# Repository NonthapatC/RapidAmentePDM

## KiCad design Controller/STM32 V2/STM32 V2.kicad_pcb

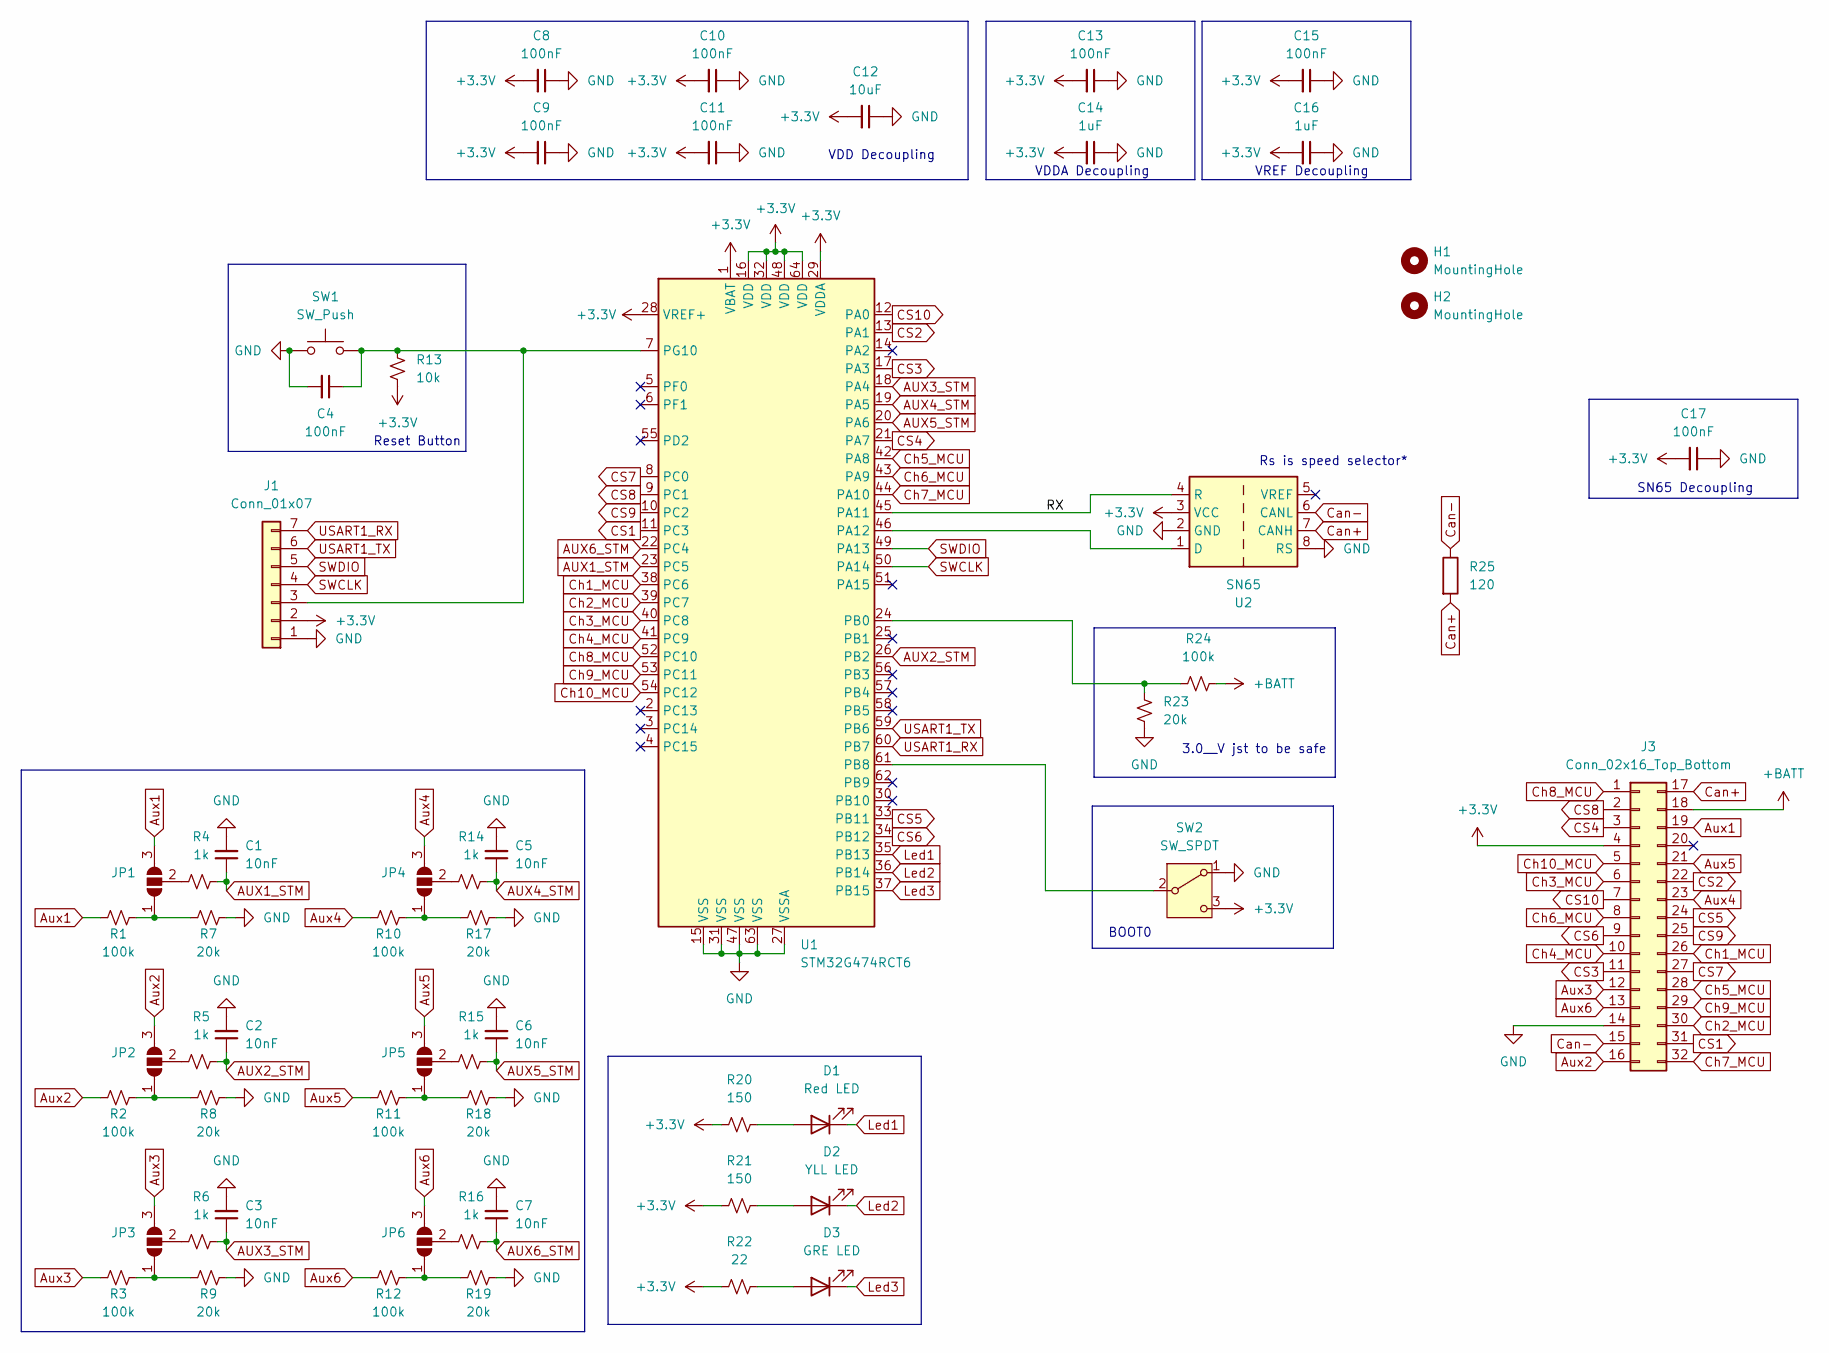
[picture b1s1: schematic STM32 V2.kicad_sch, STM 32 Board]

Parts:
C1, C2, C3, C5, C6, C7: 10nF; C_0805_2012Metric_Pad1.18x1.45mm_HandSolder
C4, C8, C9, C10, C11, C13, C15, C17: 100nF; C_0805_2012Metric_Pad1.18x1.45mm_HandSolder
C12: 10uF; C_0805_2012Metric_Pad1.18x1.45mm_HandSolder
C14, C16: 1uF; C_0805_2012Metric_Pad1.18x1.45mm_HandSolder
D1: Red LED; LED_0805_2012Metric_Pad1.15x1.40mm_HandSolder
D2: YLL LED; LED_0805_2012Metric_Pad1.15x1.40mm_HandSolder
D3: GRE LED; LED_0805_2012Metric_Pad1.15x1.40mm_HandSolder
H1, H2: MountingHole; MountingHole_NPTH_3.5_6.25SB
J1: Conn_01x07; PinSocket_1x07_P2.54mm_Vertical
J3: Conn_02x16_Top_Bottom; PinSocket_2x16_P2.54mm_Vertical
JP1, JP2, JP3, JP4, JP5, JP6: SolderJumper_3_Open; SolderJumper-3_P1.3mm_Open_RoundedPad1.0x1.5mm_NumberLabels
R1, R2, R3, R10, R11, R12, R24: 100k; R_0805_2012Metric_Pad1.20x1.40mm_HandSolder
R4, R5, R6, R14, R15, R16: 1k; R_0805_2012Metric_Pad1.20x1.40mm_HandSolder
R7, R8, R9, R17, R18, R19, R23: 20k; R_0805_2012Metric_Pad1.20x1.40mm_HandSolder
R13: 10k; R_0805_2012Metric_Pad1.20x1.40mm_HandSolder
R20, R21: 150; R_0805_2012Metric_Pad1.20x1.40mm_HandSolder
R22: 22; R_0805_2012Metric_Pad1.20x1.40mm_HandSolder
R25: 120; R_0805_2012Metric_Pad1.20x1.40mm_HandSolder
SW1: SW_Push; SW_SPST_PTS647_Sx38
SW2: SW_SPDT; HOOYA MK-12D13G4-B
U1: STM32G474RCT6; LQFP-64_10x10mm_P0.5mm
U2: SN65; SOIC-8_3.9x4.9mm_P1.27mm

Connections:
+3.3V: C8.2, C9.2, C10.2, C11.2, C12.2, C13.2, C14.2, C15.2, C16.2, C17.2, J1.2, J3.4, R13.2, R20.2, R21.2, R22.2, SW2.3 (C), U1.1 (VBAT), U1.16 (VDD), U1.28 (VREF+), U1.29 (VDDA), U1.32 (VDD), U1.48 (VDD), U1.64 (VDD), U2.3 (VCC)
+BATT: J3.18, R24.2
/RX: U1.45 (PA11), U2.4 (R)
AUX1_STM: C1.1, R4.2, U1.23 (PC5)
AUX2_STM: C2.1, R5.2, U1.26 (PB2)
AUX3_STM: C3.1, R6.2, U1.18 (PA4)
AUX4_STM: C5.1, R14.2, U1.19 (PA5)
AUX5_STM: C6.1, R15.2, U1.20 (PA6)
AUX6_STM: C7.1, R16.2, U1.22 (PC4)
Aux1: J3.19, JP1.3 (B), R1.1
Aux2: J3.16, JP2.3 (B), R2.1
Aux3: J3.12, JP3.3 (B), R3.1
Aux4: J3.23, JP4.3 (B), R10.1
Aux5: J3.21, JP5.3 (B), R11.1
Aux6: J3.13, JP6.3 (B), R12.1
CS1: J3.31, U1.11 (PC3)
CS2: J3.22, U1.13 (PA1)
CS3: J3.11, U1.17 (PA3)
CS4: J3.3, U1.21 (PA7)
CS5: J3.24, U1.33 (PB11)
CS6: J3.9, U1.34 (PB12)
CS7: J3.27, U1.8 (PC0)
CS8: J3.2, U1.9 (PC1)
CS9: J3.25, U1.10 (PC2)
CS10: J3.7, U1.12 (PA0)
Can+: J3.17, R25.2, U2.7 (CANH)
Can-: J3.15, R25.1, U2.6 (CANL)
Ch1_MCU: J3.26, U1.38 (PC6)
Ch2_MCU: J3.30, U1.39 (PC7)
Ch3_MCU: J3.6, U1.40 (PC8)
Ch4_MCU: J3.10, U1.41 (PC9)
Ch5_MCU: J3.28, U1.42 (PA8)
Ch6_MCU: J3.8, U1.43 (PA9)
Ch7_MCU: J3.32, U1.44 (PA10)
Ch8_MCU: J3.1, U1.52 (PC10)
Ch9_MCU: J3.29, U1.53 (PC11)
Ch10_MCU: J3.5, U1.54 (PC12)
GND: C1.2, C2.2, C3.2, C4.2, C5.2, C6.2, C7.2, C8.1, C9.1, C10.1, C11.1, C12.1, C13.1, C14.1, C15.1, C16.1, C17.1, J1.1, J3.14, R7.2, R8.2, R9.2, R17.2, R18.2, R19.2, R23.1, SW1.1, SW2.1 (A), U1.15 (VSS), U1.27 (VSSA), U1.31 (VSS), U1.47 (VSS), U1.63 (VSS), U2.2 (GND), U2.8 (RS)
Led1: D1.1 (K), U1.35 (PB13)
Led2: D2.1 (K), U1.36 (PB14)
Led3: D3.1 (K), U1.37 (PB15)
unnamed: D1.2 (A), R20.1
unnamed: D2.2 (A), R21.1
unnamed: D3.2 (A), R22.1
unnamed: C4.1, J1.3, R13.1, SW1.2, U1.7 (PG10)
unnamed: JP1.1 (A), R1.2, R7.1
unnamed: JP1.2 (C), R4.1
unnamed: JP2.1 (A), R2.2, R8.1
unnamed: JP2.2 (C), R5.1
unnamed: JP3.1 (A), R3.2, R9.1
unnamed: JP3.2 (C), R6.1
unnamed: JP4.1 (A), R10.2, R17.1
unnamed: JP4.2 (C), R14.1
unnamed: JP5.1 (A), R11.2, R18.1
unnamed: JP5.2 (C), R15.1
unnamed: JP6.1 (A), R12.2, R19.1
unnamed: JP6.2 (C), R16.1
unnamed: SW2.2 (B), U1.61 (PB8)
unnamed: U1.46 (PA12), U2.1 (D)
unnamed: R23.2, R24.1, U1.24 (PB0)
SWCLK: J1.4, U1.50 (PA14)
SWDIO: J1.5, U1.49 (PA13)
USART1_RX: J1.7, U1.60 (PB7)
USART1_TX: J1.6, U1.59 (PB6)

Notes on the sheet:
BOOT0
SN65 Decoupling
VDD Decoupling
Reset Button
VREF Decoupling
VDDA Decoupling
3.0__V jst to be safe
Rs is speed selector*

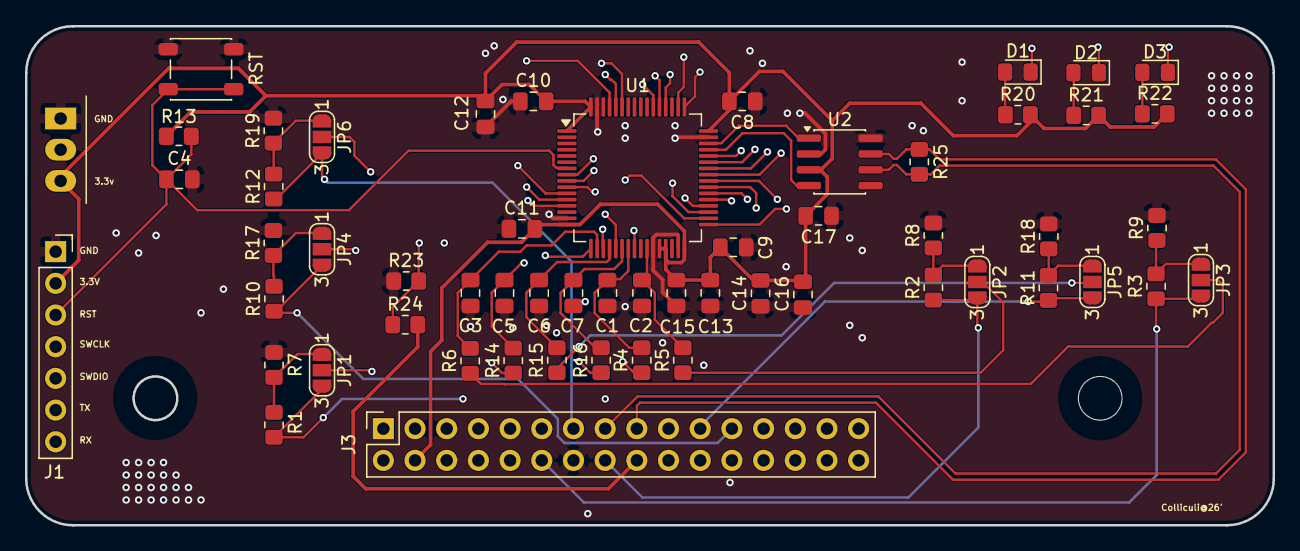
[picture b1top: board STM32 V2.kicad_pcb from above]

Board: 4 copper layers, 100.0 x 40.0 mm, 59 parts (0 on the bottom side), 64 nets.

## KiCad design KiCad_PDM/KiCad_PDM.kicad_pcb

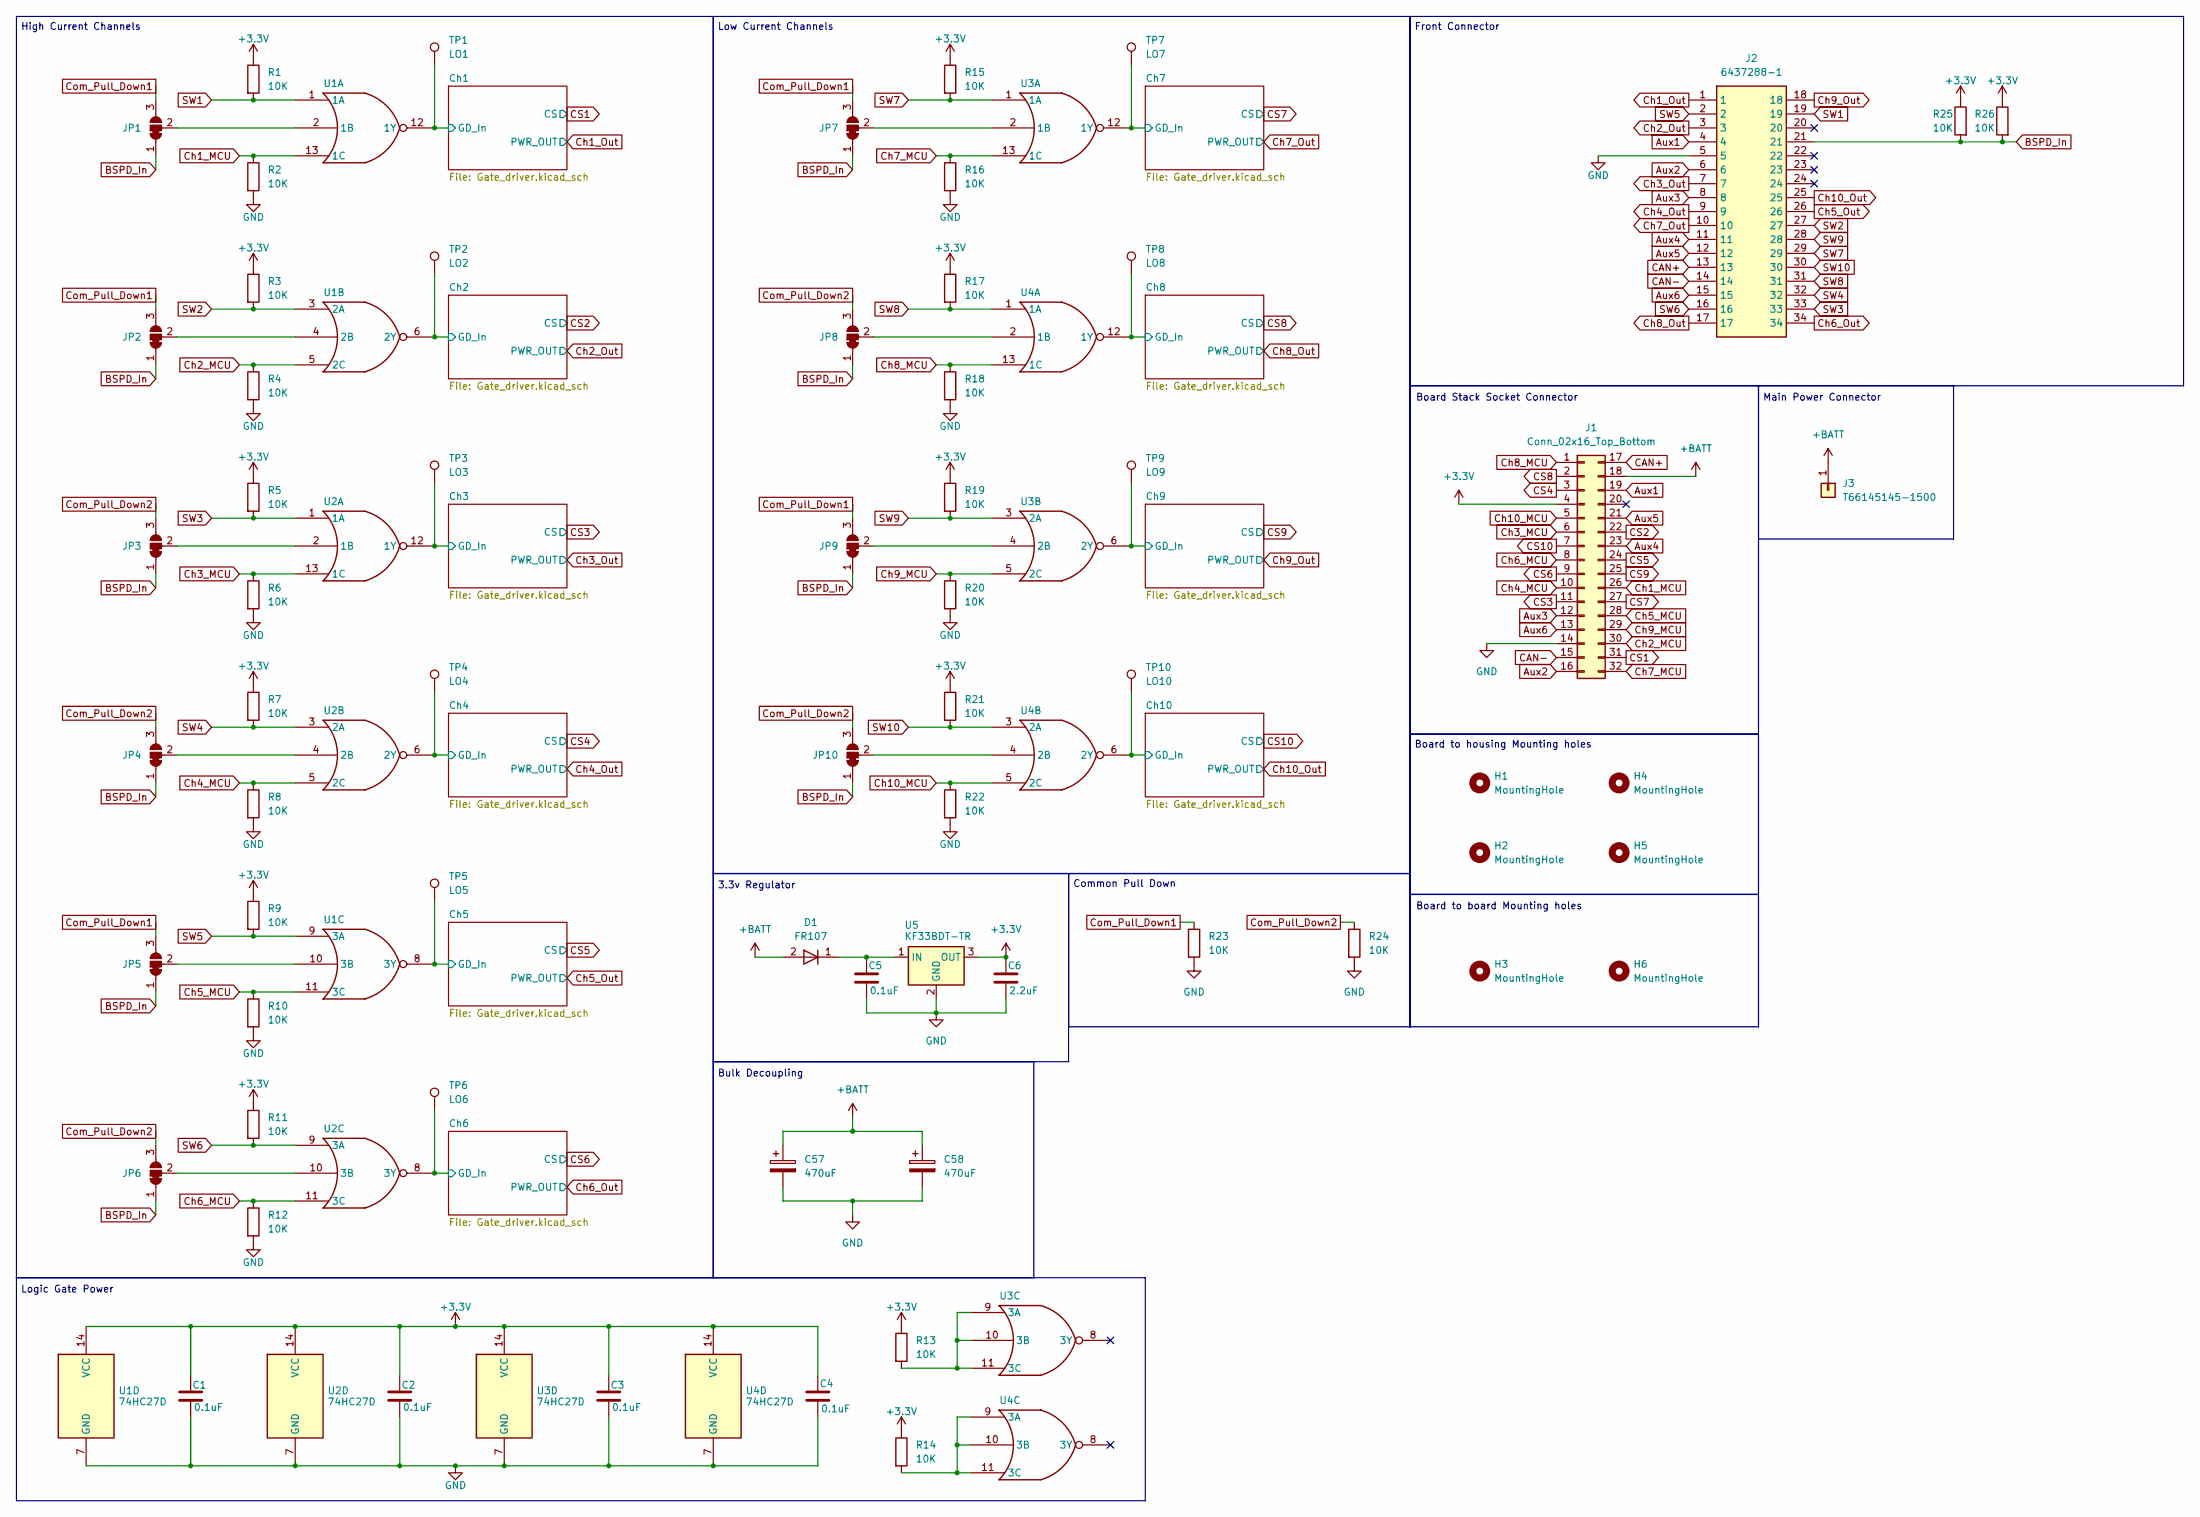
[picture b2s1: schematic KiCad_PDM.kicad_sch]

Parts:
C1, C2, C3, C4, C5: 0.1uF; C_0805_2012Metric_Pad1.18x1.45mm_HandSolder
C6: 2.2uF; C_0805_2012Metric_Pad1.18x1.45mm_HandSolder
C57, C58: 470uF; CP_Radial_D8.0mm_P2.50mm
D1: FR107; D_SOD-123
H1, H2, H3, H4, H5, H6: MountingHole; MountingHole_NPTH_3.5_6.25SB
J1: Conn_02x16_Top_Bottom; PinSocket_2x16_P2.54mm_Vertical
J2: 6437288-1; Mouser Part Number 571-6437288-1
J3: T66145145-1500; XFCN T66145145-1500
JP1, JP2, JP3, JP4, JP5, JP6, JP7, JP8, JP9, JP10: SolderJumper_3_Bridged12; SolderJumper-3_P1.3mm_Bridged2Bar12_RoundedPad1.0x1.5mm_Num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
R1, R2, R3, R4, R5, R6, R7, R8, R9, R10, R11, R12, R13, R14, R15, R16, R17, R18, R19, R20, R21, R22, R23, R24, R25, R26: 10K; R_0805_2012Metric_Pad1.20x1.40mm_HandSolder
TP1: LO1; Custom_Testpad
TP2: LO2; Custom_Testpad
TP3: LO3; Custom_Testpad
TP4: LO4; Custom_Testpad
TP5: LO5; Custom_Testpad
TP6: LO6; Custom_Testpad
TP7: LO7; Custom_Testpad
TP8: LO8; Custom_Testpad
TP9: LO9; Custom_Testpad
TP10: LO10; Custom_Testpad
U1, U2, U3, U4: 74HC27D; SOIC-14_3.9x8.7mm_P1.27mm
U5: KF33BDT-TR; TO-252-2

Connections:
+3.3V: C1.1, C2.1, C3.1, C4.1, C6.1, J1.4, R1.1, R3.1, R5.1, R7.1, R9.1, R11.1, R13.1, R14.1, R15.1, R17.1, R19.1, R21.1, R25.1, R26.1, U1.14 (VCC), U2.14 (VCC), U3.14 (VCC), U4.14 (VCC), U5.3 (OUT); also elsewhere on the board
+BATT: C57.1, C58.1, D1.2, J1.18, J3.1 (Pin_1_1); also elsewhere on the board
/Ch1/GD_In: TP1.1 (1_1), U1.12 (1Y); also elsewhere on the board
/Ch2/GD_In: TP2.1 (1_1), U1.6 (2Y); also elsewhere on the board
/Ch3/GD_In: TP3.1 (1_1), U2.12 (1Y); also elsewhere on the board
/Ch4/GD_In: TP4.1 (1_1), U2.6 (2Y); also elsewhere on the board
/Ch5/GD_In: TP5.1 (1_1), U1.8 (3Y); also elsewhere on the board
/Ch6/GD_In: TP6.1 (1_1), U2.8 (3Y); also elsewhere on the board
/Ch7/GD_In: TP7.1 (1_1), U3.12 (1Y); also elsewhere on the board
/Ch8/GD_In: TP8.1 (1_1), U4.12 (1Y); also elsewhere on the board
/Ch9/GD_In: TP9.1 (1_1), U3.6 (2Y); also elsewhere on the board
/Ch10/GD_In: TP10.1 (1_1), U4.6 (2Y); also elsewhere on the board
Aux1: J1.19, J2.4
Aux2: J1.16, J2.6
Aux3: J1.12, J2.8
Aux4: J1.23, J2.11
Aux5: J1.21, J2.12
Aux6: J1.13, J2.15
BSPD_In: J2.21, JP1.1 (A), JP2.1 (A), JP3.1 (A), JP4.1 (A), JP5.1 (A), JP6.1 (A), JP7.1 (A), JP8.1 (A), JP9.1 (A), JP10.1 (A), R25.2, R26.2
CAN+: J1.17, J2.13
CAN-: J1.15, J2.14
CS1: J1.31; also elsewhere on the board
CS2: J1.22; also elsewhere on the board
CS3: J1.11; also elsewhere on the board
CS4: J1.3; also elsewhere on the board
CS5: J1.24; also elsewhere on the board
CS6: J1.9; also elsewhere on the board
CS7: J1.27; also elsewhere on the board
CS8: J1.2; also elsewhere on the board
CS9: J1.25; also elsewhere on the board
CS10: J1.7; also elsewhere on the board
Ch1_MCU: J1.26, R2.1, U1.13 (1C)
Ch1_Out: J2.1; also elsewhere on the board
Ch2_MCU: J1.30, R4.1, U1.5 (2C)
Ch2_Out: J2.3; also elsewhere on the board
Ch3_MCU: J1.6, R6.1, U2.13 (1C)
Ch3_Out: J2.7; also elsewhere on the board
Ch4_MCU: J1.10, R8.1, U2.5 (2C)
Ch4_Out: J2.9; also elsewhere on the board
Ch5_MCU: J1.28, R10.1, U1.11 (3C)
Ch5_Out: J2.26; also elsewhere on the board
Ch6_MCU: J1.8, R12.1, U2.11 (3C)
Ch6_Out: J2.34; also elsewhere on the board
Ch7_MCU: J1.32, R16.1, U3.13 (1C)
Ch7_Out: J2.10; also elsewhere on the board
Ch8_MCU: J1.1, R18.1, U4.13 (1C)
Ch8_Out: J2.17; also elsewhere on the board
Ch9_MCU: J1.29, R20.1, U3.5 (2C)
Ch9_Out: J2.18; also elsewhere on the board
Ch10_MCU: J1.5, R22.1, U4.5 (2C)
Ch10_Out: J2.25; also elsewhere on the board
Com_Pull_Down1: JP1.3 (B), JP2.3 (B), JP5.3 (B), JP7.3 (B), JP9.3 (B), R23.1
Com_Pull_Down2: JP3.3 (B), JP4.3 (B), JP6.3 (B), JP8.3 (B), JP10.3 (B), R24.1
GND: C1.2, C2.2, C3.2, C4.2, C5.2, C6.2, C57.2, C58.2, J1.14, J2.5, R2.2, R4.2, R6.2, R8.2, R10.2, R12.2, R16.2, R18.2, R20.2, R22.2, R23.2, R24.2, U1.7 (GND), U2.7 (GND), U3.7 (GND), U4.7 (GND), U5.2 (GND); also elsewhere on the board
unnamed: JP1.2 (C), U1.2 (1B)
unnamed: JP2.2 (C), U1.4 (2B)
unnamed: JP3.2 (C), U2.2 (1B)
unnamed: JP4.2 (C), U2.4 (2B)
unnamed: JP5.2 (C), U1.10 (3B)
unnamed: JP6.2 (C), U2.10 (3B)
unnamed: JP7.2 (C), U3.2 (1B)
unnamed: JP8.2 (C), U4.2 (1B)
unnamed: JP9.2 (C), U3.4 (2B)
unnamed: JP10.2 (C), U4.4 (2B)
unnamed: R13.2, U3.9 (3A), U3.10 (3B), U3.11 (3C)
unnamed: R14.2, U4.9 (3A), U4.10 (3B), U4.11 (3C)
unnamed: C5.1, D1.1, U5.1 (IN)
SW1: J2.19, R1.2, U1.1 (1A)
SW2: J2.27, R3.2, U1.3 (2A)
SW3: J2.33, R5.2, U2.1 (1A)
SW4: J2.32, R7.2, U2.3 (2A)
SW5: J2.2, R9.2, U1.9 (3A)
SW6: J2.16, R11.2, U2.9 (3A)
SW7: J2.29, R15.2, U3.1 (1A)
SW8: J2.31, R17.2, U4.1 (1A)
SW9: J2.28, R19.2, U3.3 (2A)
SW10: J2.30, R21.2, U4.3 (2A)

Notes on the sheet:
Bulk Decoupling
3.3v Regulator
Board Stack Socket Connector
Common Pull Down
Low Current Channels
Logic Gate Power
Front Connector
High Current Channels
Main Power Connector
Board to housing Mounting holes
Board to board Mounting holes

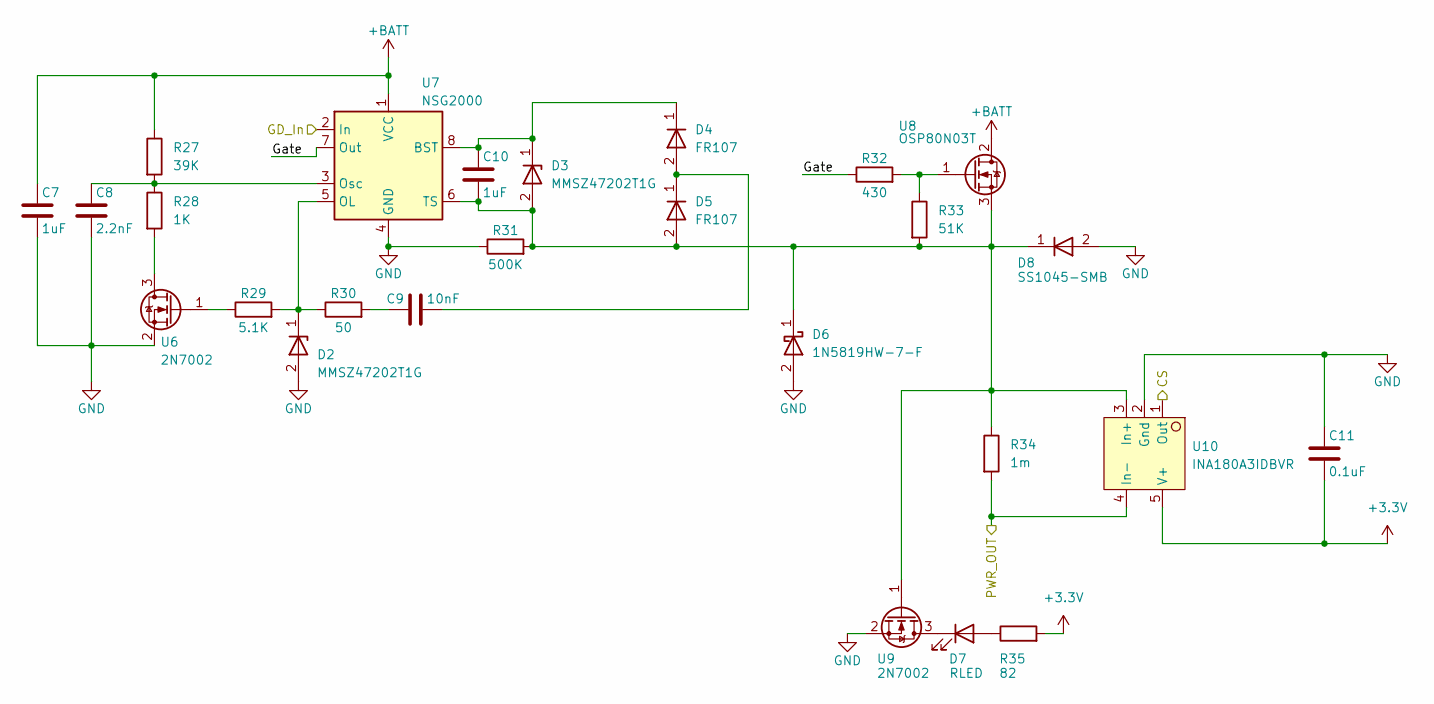
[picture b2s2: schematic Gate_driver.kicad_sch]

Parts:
C7, C10: 1uF; C_0805_2012Metric_Pad1.18x1.45mm_HandSolder
C8: 2.2nF; C_0805_2012Metric_Pad1.18x1.45mm_HandSolder
C9: 10nF; C_0805_2012Metric_Pad1.18x1.45mm_HandSolder
C11: 0.1uF; C_0805_2012Metric_Pad1.18x1.45mm_HandSolder
D2, D3: MMSZ47202T1G; D_SOD-123
D4, D5: FR107; D_SOD-123
D6: 1N5819HW-7-F; D_SOD-123
D7: RLED; LED_0805_2012Metric_Pad1.15x1.40mm_HandSolder
D8: SS1045-SMB; D_SMB_Handsoldering
R27: 39K; R_0805_2012Metric_Pad1.20x1.40mm_HandSolder
R28: 1K; R_0805_2012Metric_Pad1.20x1.40mm_HandSolder
R29: 5.1K; R_0805_2012Metric_Pad1.20x1.40mm_HandSolder
R30: 50; R_0805_2012Metric_Pad1.20x1.40mm_HandSolder
R31: 500K; R_0805_2012Metric_Pad1.20x1.40mm_HandSolder
R32: 430; R_0805_2012Metric_Pad1.20x1.40mm_HandSolder
R33: 51K; R_0805_2012Metric_Pad1.20x1.40mm_HandSolder
R34: 1m; R_2512_6332Metric_Pad1.40x3.35mm_HandSolder
R35: 82; R_0805_2012Metric_Pad1.20x1.40mm_HandSolder
U6, U9: 2N7002; SOT-23_Handsoldering
U7: NSG2000; SOIC-8_3.9x4.9mm_P1.27mm
U8: OSP80N03T; Bolt_head_clearance_TO-220-3_Horizontal_TabUp
U10: INA180A3IDBVR; SOT-23-5_HandSoldering

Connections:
+3.3V: C11.2, R35.2, U10.5 (V+); also elsewhere on the board
+BATT: C7.1, R27.1, U7.1 (VCC), U8.2 (Drain); also elsewhere on the board
/Ch1/GD_In: U7.2 (In); also elsewhere on the board
/Ch1/Gate: R32.1, U7.7 (Out)
CS1: U10.1 (Out); also elsewhere on the board
Ch1_Out: R34.2, U10.4 (In-); also elsewhere on the board
GND: C7.2, C8.2, C11.1, D2.2, D6.2 (A), D8.2, R31.1, U6.2 (S), U7.4 (GND), U9.2 (S), U10.2 (Gnd); also elsewhere on the board
unnamed: C9.1, R30.2
unnamed: C9.2, D4.2, D5.1
unnamed: C10.2, D3.2, D5.2, D6.1 (K), D8.1, R31.2, R33.2, R34.1, U7.6 (TS), U8.3 (Source), U9.1 (G), U10.3 (In+)
unnamed: D7.2 (A), R35.1
unnamed: D7.1 (K), U9.3 (D)
unnamed: R28.2, U6.3 (D)
unnamed: R29.1, U6.1 (G)
unnamed: C10.1, D3.1, D4.1, U7.8 (BST)
unnamed: D2.1, R29.2, R30.1, U7.5 (OL)
unnamed: C8.1, R27.2, R28.1, U7.3 (Osc)
unnamed: R32.2, R33.1, U8.1 (Gate)

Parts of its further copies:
C12, C15, C17, C20, C22, C25, C27, C30, C32, C35, C37, C40, C42, C45, C47, C50, C52, C55: 1uF; C_0805_2012Metric_Pad1.18x1.45mm_HandSolder
C13, C18, C23, C28, C33, C38, C43, C48, C53: 2.2nF; C_0805_2012Metric_Pad1.18x1.45mm_HandSolder
C14, C19, C24, C29, C34, C39, C44, C49, C54: 10nF; C_0805_2012Metric_Pad1.18x1.45mm_HandSolder
C16, C21, C26, C31, C36, C41, C46, C51, C56: 0.1uF; C_0805_2012Metric_Pad1.18x1.45mm_HandSolder
D9, D10, D16, D17, D23, D24, D30, D31, D37, D38, D44, D45, D51, D52, D58, D59, D65, D66: MMSZ47202T1G; D_SOD-123
D11, D12, D18, D19, D25, D26, D32, D33, D39, D40, D46, D47, D53, D54, D60, D61, D67, D68: FR107; D_SOD-123
D13, D20, D27, D34, D41, D48, D55, D62, D69: 1N5819HW-7-F; D_SOD-123
D14, D21, D28, D35, D42, D49, D56, D63, D70: RLED; LED_0805_2012Metric_Pad1.15x1.40mm_HandSolder
D15, D22, D29, D36, D43, D50, D57, D64, D71: SS1045-SMB; D_SMB_Handsoldering
R36, R45, R54, R63, R72, R81, R90, R99, R108: 39K; R_0805_2012Metric_Pad1.20x1.40mm_HandSolder
R37, R46, R55, R64, R73, R82, R91, R100, R109: 1K; R_0805_2012Metric_Pad1.20x1.40mm_HandSolder
R38, R47, R56, R65, R74, R83, R92, R101, R110: 5.1K; R_0805_2012Metric_Pad1.20x1.40mm_HandSolder
R39, R48, R57, R66, R75, R84, R93, R102, R111: 50; R_0805_2012Metric_Pad1.20x1.40mm_HandSolder
R40, R49, R58, R67, R76, R85, R94, R103, R112: 500K; R_0805_2012Metric_Pad1.20x1.40mm_HandSolder
R41, R50, R59, R68, R77, R86, R95, R104, R113: 430; R_0805_2012Metric_Pad1.20x1.40mm_HandSolder
R42, R51, R60, R69, R78, R87, R96, R105, R114: 51K; R_0805_2012Metric_Pad1.20x1.40mm_HandSolder
R43, R52, R61, R70, R79, R88, R97, R106, R115: 1m; R_2512_6332Metric_Pad1.40x3.35mm_HandSolder
R44, R53, R62, R71, R80, R89, R98, R107, R116: 82; R_0805_2012Metric_Pad1.20x1.40mm_HandSolder
U11, U14, U16, U19, U21, U24, U26, U29, U31, U34, U36, U39, U41, U44, U46, U49, U51, U54: 2N7002; SOT-23_Handsoldering
U12, U17, U22, U27, U32, U37, U42, U47, U52: NSG2000; SOIC-8_3.9x4.9mm_P1.27mm
U13, U18, U23, U28, U33, U38, U43, U48, U53: OSP80N03T; Bolt_head_clearance_TO-220-3_Horizontal_TabUp
U15, U20, U25, U30, U35, U40, U45, U50, U55: INA180A3IDBVR; SOT-23-5_HandSoldering

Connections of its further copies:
+3.3V: C16.2, C21.2, C26.2, C31.2, C36.2, C41.2, C46.2, C51.2, C56.2, R44.2, R53.2, R62.2, R71.2, R80.2, R89.2, R98.2, R107.2, R116.2, U15.5 (V+), U20.5 (V+), U25.5 (V+), U30.5 (V+), U35.5 (V+), U40.5 (V+), U45.5 (V+), U50.5 (V+), U55.5 (V+); also elsewhere on the board
+BATT: C12.1, C17.1, C22.1, C27.1, C32.1, C37.1, C42.1, C47.1, C52.1, R36.1, R45.1, R54.1, R63.1, R72.1, R81.1, R90.1, R99.1, R108.1, U12.1 (VCC), U13.2 (Drain), U17.1 (VCC), U18.2 (Drain), U22.1 (VCC), U23.2 (Drain), U27.1 (VCC), U28.2 (Drain), U32.1 (VCC), U33.2 (Drain), U37.1 (VCC), U38.2 (Drain), U42.1 (VCC), U43.2 (Drain), U47.1 (VCC), U48.2 (Drain), U52.1 (VCC), U53.2 (Drain); also elsewhere on the board
/Ch2/GD_In: U12.2 (In); also elsewhere on the board
/Ch2/Gate: R41.1, U12.7 (Out)
/Ch3/GD_In: U17.2 (In); also elsewhere on the board
/Ch3/Gate: R50.1, U17.7 (Out)
/Ch4/GD_In: U22.2 (In); also elsewhere on the board
/Ch4/Gate: R59.1, U22.7 (Out)
/Ch5/GD_In: U27.2 (In); also elsewhere on the board
/Ch5/Gate: R68.1, U27.7 (Out)
/Ch6/GD_In: U32.2 (In); also elsewhere on the board
/Ch6/Gate: R77.1, U32.7 (Out)
/Ch7/GD_In: U37.2 (In); also elsewhere on the board
/Ch7/Gate: R86.1, U37.7 (Out)
/Ch8/GD_In: U42.2 (In); also elsewhere on the board
/Ch8/Gate: R95.1, U42.7 (Out)
/Ch9/GD_In: U47.2 (In); also elsewhere on the board
/Ch9/Gate: R104.1, U47.7 (Out)
/Ch10/GD_In: U52.2 (In); also elsewhere on the board
/Ch10/Gate: R113.1, U52.7 (Out)
CS2: U15.1 (Out); also elsewhere on the board
CS3: U20.1 (Out); also elsewhere on the board
CS4: U25.1 (Out); also elsewhere on the board
CS5: U30.1 (Out); also elsewhere on the board
CS6: U35.1 (Out); also elsewhere on the board
CS7: U40.1 (Out); also elsewhere on the board
CS8: U45.1 (Out); also elsewhere on the board
CS9: U50.1 (Out); also elsewhere on the board
CS10: U55.1 (Out); also elsewhere on the board
Ch2_Out: R43.2, U15.4 (In-); also elsewhere on the board
Ch3_Out: R52.2, U20.4 (In-); also elsewhere on the board
Ch4_Out: R61.2, U25.4 (In-); also elsewhere on the board
Ch5_Out: R70.2, U30.4 (In-); also elsewhere on the board
Ch6_Out: R79.2, U35.4 (In-); also elsewhere on the board
Ch7_Out: R88.2, U40.4 (In-); also elsewhere on the board
Ch8_Out: R97.2, U45.4 (In-); also elsewhere on the board
Ch9_Out: R106.2, U50.4 (In-); also elsewhere on the board
Ch10_Out: R115.2, U55.4 (In-); also elsewhere on the board
GND: C12.2, C13.2, C16.1, C17.2, C18.2, C21.1, C22.2, C23.2, C26.1, C27.2, C28.2, C31.1, C32.2, C33.2, C36.1, C37.2, C38.2, C41.1, C42.2, C43.2, C46.1, C47.2, C48.2, C51.1, C52.2, C53.2, C56.1, D9.2, D13.2 (A), D15.2, D16.2, D20.2 (A), D22.2, D23.2, D27.2 (A), D29.2, D30.2, D34.2 (A), D36.2, D37.2, D41.2 (A), D43.2, D44.2, D48.2 (A), D50.2, D51.2, D55.2 (A), D57.2, D58.2, D62.2 (A), D64.2, D65.2, D69.2 (A), D71.2, R40.1, R49.1, R58.1, R67.1, R76.1, R85.1, R94.1, R103.1, R112.1, U11.2 (S), U12.4 (GND), U14.2 (S), U15.2 (Gnd), U16.2 (S), U17.4 (GND), U19.2 (S), U20.2 (Gnd), U21.2 (S), U22.4 (GND), U24.2 (S), U25.2 (Gnd), U26.2 (S), U27.4 (GND), U29.2 (S), U30.2 (Gnd), U31.2 (S), U32.4 (GND), U34.2 (S), U35.2 (Gnd), U36.2 (S), U37.4 (GND), U39.2 (S), U40.2 (Gnd), U41.2 (S), U42.4 (GND), U44.2 (S), U45.2 (Gnd), U46.2 (S), U47.4 (GND), U49.2 (S), U50.2 (Gnd), U51.2 (S), U52.4 (GND), U54.2 (S), U55.2 (Gnd); also elsewhere on the board
unnamed: C14.1, R39.2
unnamed: C14.2, D11.2, D12.1
unnamed: C19.1, R48.2
unnamed: C19.2, D18.2, D19.1
unnamed: C24.1, R57.2
unnamed: C24.2, D25.2, D26.1
unnamed: C29.1, R66.2
unnamed: C29.2, D32.2, D33.1
unnamed: C34.1, R75.2
unnamed: C34.2, D39.2, D40.1
unnamed: C39.1, R84.2
unnamed: C39.2, D46.2, D47.1
unnamed: C44.1, R93.2
unnamed: C44.2, D53.2, D54.1
unnamed: C49.1, R102.2
unnamed: C49.2, D60.2, D61.1
unnamed: C54.1, R111.2
unnamed: C54.2, D67.2, D68.1
unnamed: C15.2, D10.2, D12.2, D13.1 (K), D15.1, R40.2, R42.2, R43.1, U12.6 (TS), U13.3 (Source), U14.1 (G), U15.3 (In+)
unnamed: D14.2 (A), R44.1
unnamed: D14.1 (K), U14.3 (D)
unnamed: C20.2, D17.2, D19.2, D20.1 (K), D22.1, R49.2, R51.2, R52.1, U17.6 (TS), U18.3 (Source), U19.1 (G), U20.3 (In+)
unnamed: D21.2 (A), R53.1
unnamed: D21.1 (K), U19.3 (D)
unnamed: C25.2, D24.2, D26.2, D27.1 (K), D29.1, R58.2, R60.2, R61.1, U22.6 (TS), U23.3 (Source), U24.1 (G), U25.3 (In+)
unnamed: D28.2 (A), R62.1
unnamed: D28.1 (K), U24.3 (D)
unnamed: C30.2, D31.2, D33.2, D34.1 (K), D36.1, R67.2, R69.2, R70.1, U27.6 (TS), U28.3 (Source), U29.1 (G), U30.3 (In+)
unnamed: D35.2 (A), R71.1
unnamed: D35.1 (K), U29.3 (D)
unnamed: C35.2, D38.2, D40.2, D41.1 (K), D43.1, R76.2, R78.2, R79.1, U32.6 (TS), U33.3 (Source), U34.1 (G), U35.3 (In+)
unnamed: D42.2 (A), R80.1
unnamed: D42.1 (K), U34.3 (D)
unnamed: C40.2, D45.2, D47.2, D48.1 (K), D50.1, R85.2, R87.2, R88.1, U37.6 (TS), U38.3 (Source), U39.1 (G), U40.3 (In+)
unnamed: D49.2 (A), R89.1
unnamed: D49.1 (K), U39.3 (D)
unnamed: C45.2, D52.2, D54.2, D55.1 (K), D57.1, R94.2, R96.2, R97.1, U42.6 (TS), U43.3 (Source), U44.1 (G), U45.3 (In+)
unnamed: D56.2 (A), R98.1
unnamed: D56.1 (K), U44.3 (D)
unnamed: C50.2, D59.2, D61.2, D62.1 (K), D64.1, R103.2, R105.2, R106.1, U47.6 (TS), U48.3 (Source), U49.1 (G), U50.3 (In+)
unnamed: D63.2 (A), R107.1
unnamed: D63.1 (K), U49.3 (D)
unnamed: C55.2, D66.2, D68.2, D69.1 (K), D71.1, R112.2, R114.2, R115.1, U52.6 (TS), U53.3 (Source), U54.1 (G), U55.3 (In+)
unnamed: D70.2 (A), R116.1
unnamed: D70.1 (K), U54.3 (D)
unnamed: R37.2, U11.3 (D)
unnamed: R38.1, U11.1 (G)
unnamed: C15.1, D10.1, D11.1, U12.8 (BST)
unnamed: D9.1, R38.2, R39.1, U12.5 (OL)
unnamed: C13.1, R36.2, R37.1, U12.3 (Osc)
unnamed: R41.2, R42.1, U13.1 (Gate)
unnamed: R46.2, U16.3 (D)
unnamed: R47.1, U16.1 (G)
unnamed: C20.1, D17.1, D18.1, U17.8 (BST)
unnamed: D16.1, R47.2, R48.1, U17.5 (OL)
unnamed: C18.1, R45.2, R46.1, U17.3 (Osc)
unnamed: R50.2, R51.1, U18.1 (Gate)
unnamed: R55.2, U21.3 (D)
unnamed: R56.1, U21.1 (G)
unnamed: C25.1, D24.1, D25.1, U22.8 (BST)
unnamed: D23.1, R56.2, R57.1, U22.5 (OL)
unnamed: C23.1, R54.2, R55.1, U22.3 (Osc)
unnamed: R59.2, R60.1, U23.1 (Gate)
unnamed: R64.2, U26.3 (D)
unnamed: R65.1, U26.1 (G)
unnamed: C30.1, D31.1, D32.1, U27.8 (BST)
unnamed: D30.1, R65.2, R66.1, U27.5 (OL)
unnamed: C28.1, R63.2, R64.1, U27.3 (Osc)
unnamed: R68.2, R69.1, U28.1 (Gate)
unnamed: R73.2, U31.3 (D)
unnamed: R74.1, U31.1 (G)
unnamed: C35.1, D38.1, D39.1, U32.8 (BST)
unnamed: D37.1, R74.2, R75.1, U32.5 (OL)
unnamed: C33.1, R72.2, R73.1, U32.3 (Osc)
unnamed: R77.2, R78.1, U33.1 (Gate)
unnamed: R82.2, U36.3 (D)
unnamed: R83.1, U36.1 (G)
unnamed: C40.1, D45.1, D46.1, U37.8 (BST)
unnamed: D44.1, R83.2, R84.1, U37.5 (OL)
unnamed: C38.1, R81.2, R82.1, U37.3 (Osc)
unnamed: R86.2, R87.1, U38.1 (Gate)
unnamed: R91.2, U41.3 (D)
unnamed: R92.1, U41.1 (G)
unnamed: C45.1, D52.1, D53.1, U42.8 (BST)
unnamed: D51.1, R92.2, R93.1, U42.5 (OL)
unnamed: C43.1, R90.2, R91.1, U42.3 (Osc)
unnamed: R95.2, R96.1, U43.1 (Gate)
unnamed: R100.2, U46.3 (D)
unnamed: R101.1, U46.1 (G)
unnamed: C50.1, D59.1, D60.1, U47.8 (BST)
unnamed: D58.1, R101.2, R102.1, U47.5 (OL)
unnamed: C48.1, R99.2, R100.1, U47.3 (Osc)
unnamed: R104.2, R105.1, U48.1 (Gate)
unnamed: R109.2, U51.3 (D)
unnamed: R110.1, U51.1 (G)
unnamed: C55.1, D66.1, D67.1, U52.8 (BST)
unnamed: D65.1, R110.2, R111.1, U52.5 (OL)
unnamed: C53.1, R108.2, R109.1, U52.3 (Osc)
unnamed: R113.2, R114.1, U53.1 (Gate)
